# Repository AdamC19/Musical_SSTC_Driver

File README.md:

# Musical Solid-State Tesla Coil Project
These are the hardware source files for my 2022 revision of my musical solid-state Tesla coil driver. 

This is a completely analog design. No firmware!

## Concept
The concept is not far off from my previous design, except for a few notable differences.

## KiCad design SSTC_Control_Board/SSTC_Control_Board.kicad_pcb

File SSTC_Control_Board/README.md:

# Control Board

Below is a simplified block-diagram of the control board:

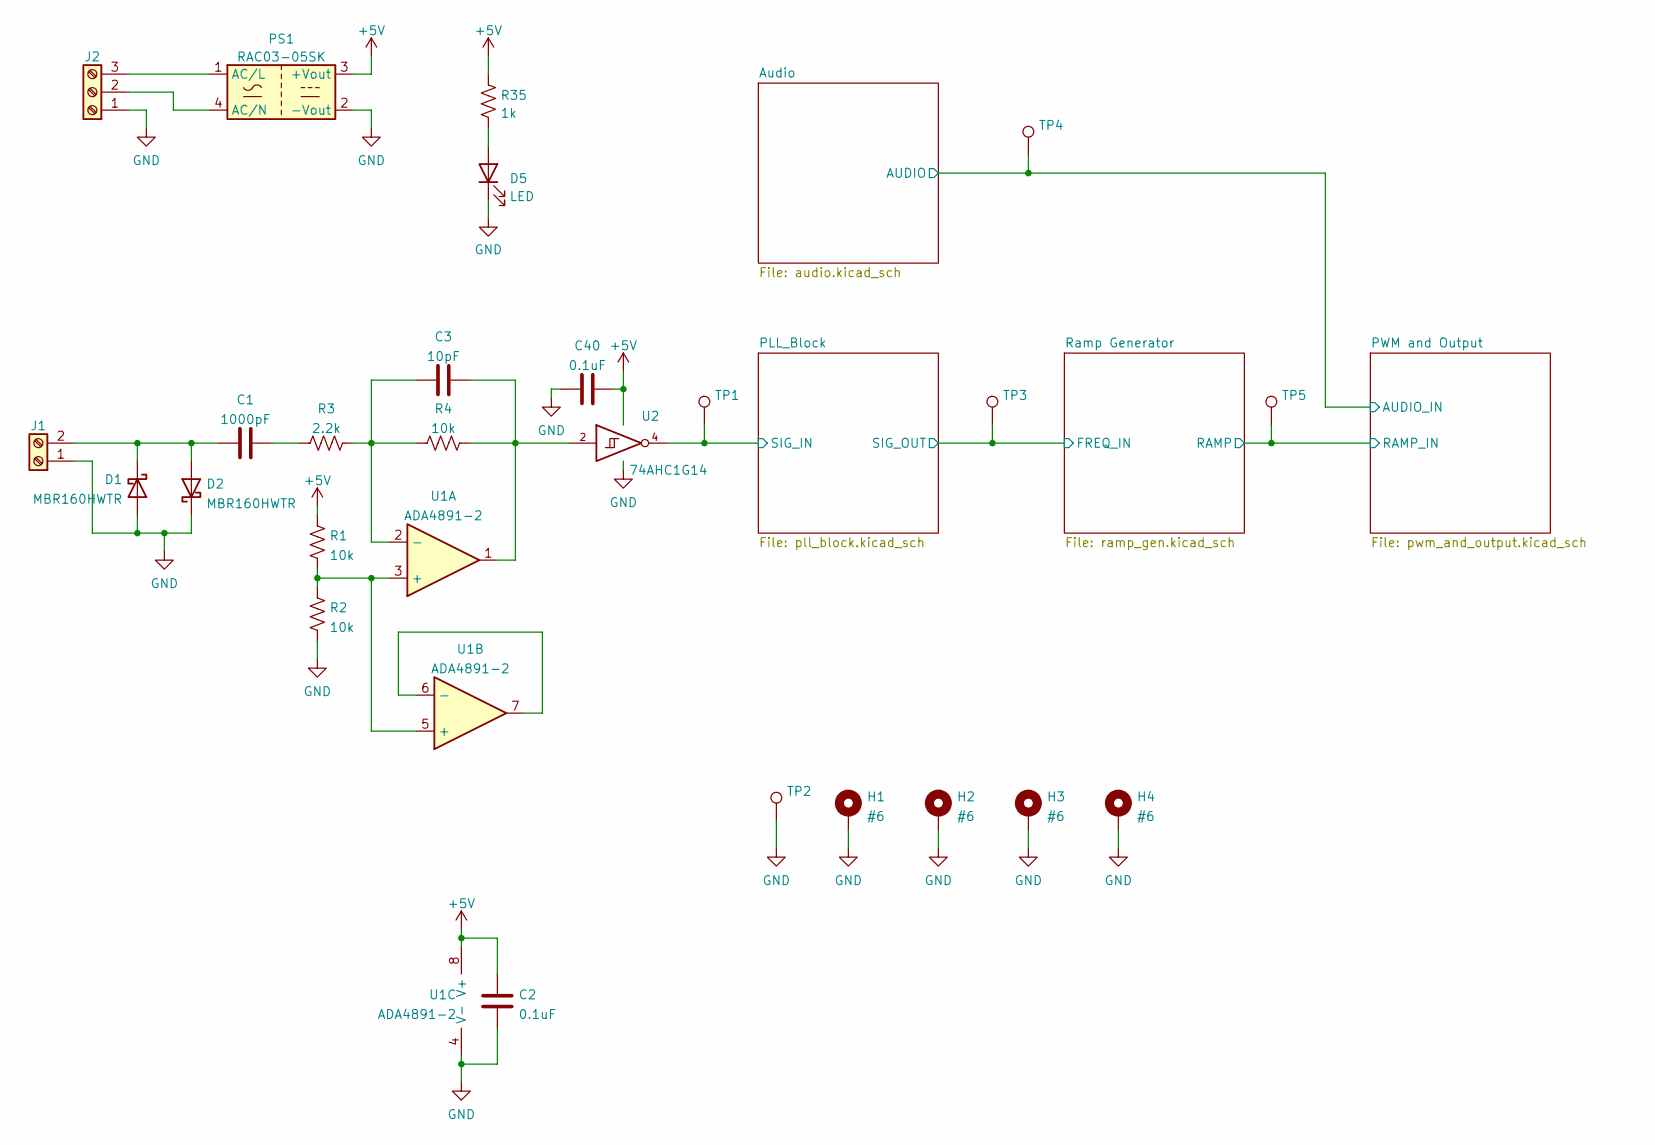
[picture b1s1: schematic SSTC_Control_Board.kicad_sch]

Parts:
C1: 1000pF; C_0603_1608Metric
C2, C40: 0.1uF; C_0603_1608Metric
C3: 10pF; C_0603_1608Metric
D1, D2: MBR160HWTR; D_SOD-123; MFG_PN MBR160HWTR
D5: LED; LED_0603_1608Metric
H1, H2, H3, H4: #6; MountingHole_3.7mm_Pad_Via
J1: Screw_Terminal_01x02; PhoenixContact_MC_1,5_2-G-3.81_1x02_P3.81mm_Horizontal
J2: Screw_Terminal_01x03; PhoenixContact_GMSTBA_2,5_3-G-7,62_1x03_P7.62mm_Horizontal
PS1: RAC03-05SK; RAC03-K; MFG_PN RAC03-05SK
R1, R2, R4: 10k; R_0805_2012Metric
R3: 2.2k; R_0805_2012Metric
R35: 1k; R_0805_2012Metric
TP1, TP2, TP3, TP4, TP5: TestPoint; TestPoint_Bridge_Pitch2.54mm_Drill1.0mm
U1: ADA4891-2; SOIC-8_3.9x4.9mm_P1.27mm
U2: 74AHC1G14; SOT-23-5

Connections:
+5V: C2.2, C40.1, PS1.3 (+Vout), R1.1, R35.2, U1.8 (V+), U2.5 (VCC); also elsewhere on the board
/Audio/AUDIO: TP4.1; also elsewhere on the board
/PLL_Block/SIG_IN: TP1.1, U2.4; also elsewhere on the board
/PLL_Block/SIG_OUT: TP3.1; also elsewhere on the board
/PWM and Output/RAMP_IN: TP5.1; also elsewhere on the board
GND: C2.1, C40.2, D1.2 (A), D2.1 (K), D5.1 (K), H1.1, H2.1, H3.1, H4.1, J1.1, J2.1, PS1.2 (-Vout), R2.2, TP2.1, U1.4 (V-), U2.3 (GND); also elsewhere on the board
unnamed: C1.1, D1.1 (K), D2.2 (A), J1.2
unnamed: C1.2, R3.1
unnamed: C3.1, R3.2, R4.1, U1.2 (-)
unnamed: C3.2, R4.2, U1.1, U2.2
unnamed: D5.2 (A), R35.1
unnamed: J2.2, PS1.4 (AC/N)
unnamed: J2.3, PS1.1 (AC/L)
unnamed: R1.2, R2.1, U1.3 (+), U1.5 (+)
unnamed: U1.6 (-), U1.7

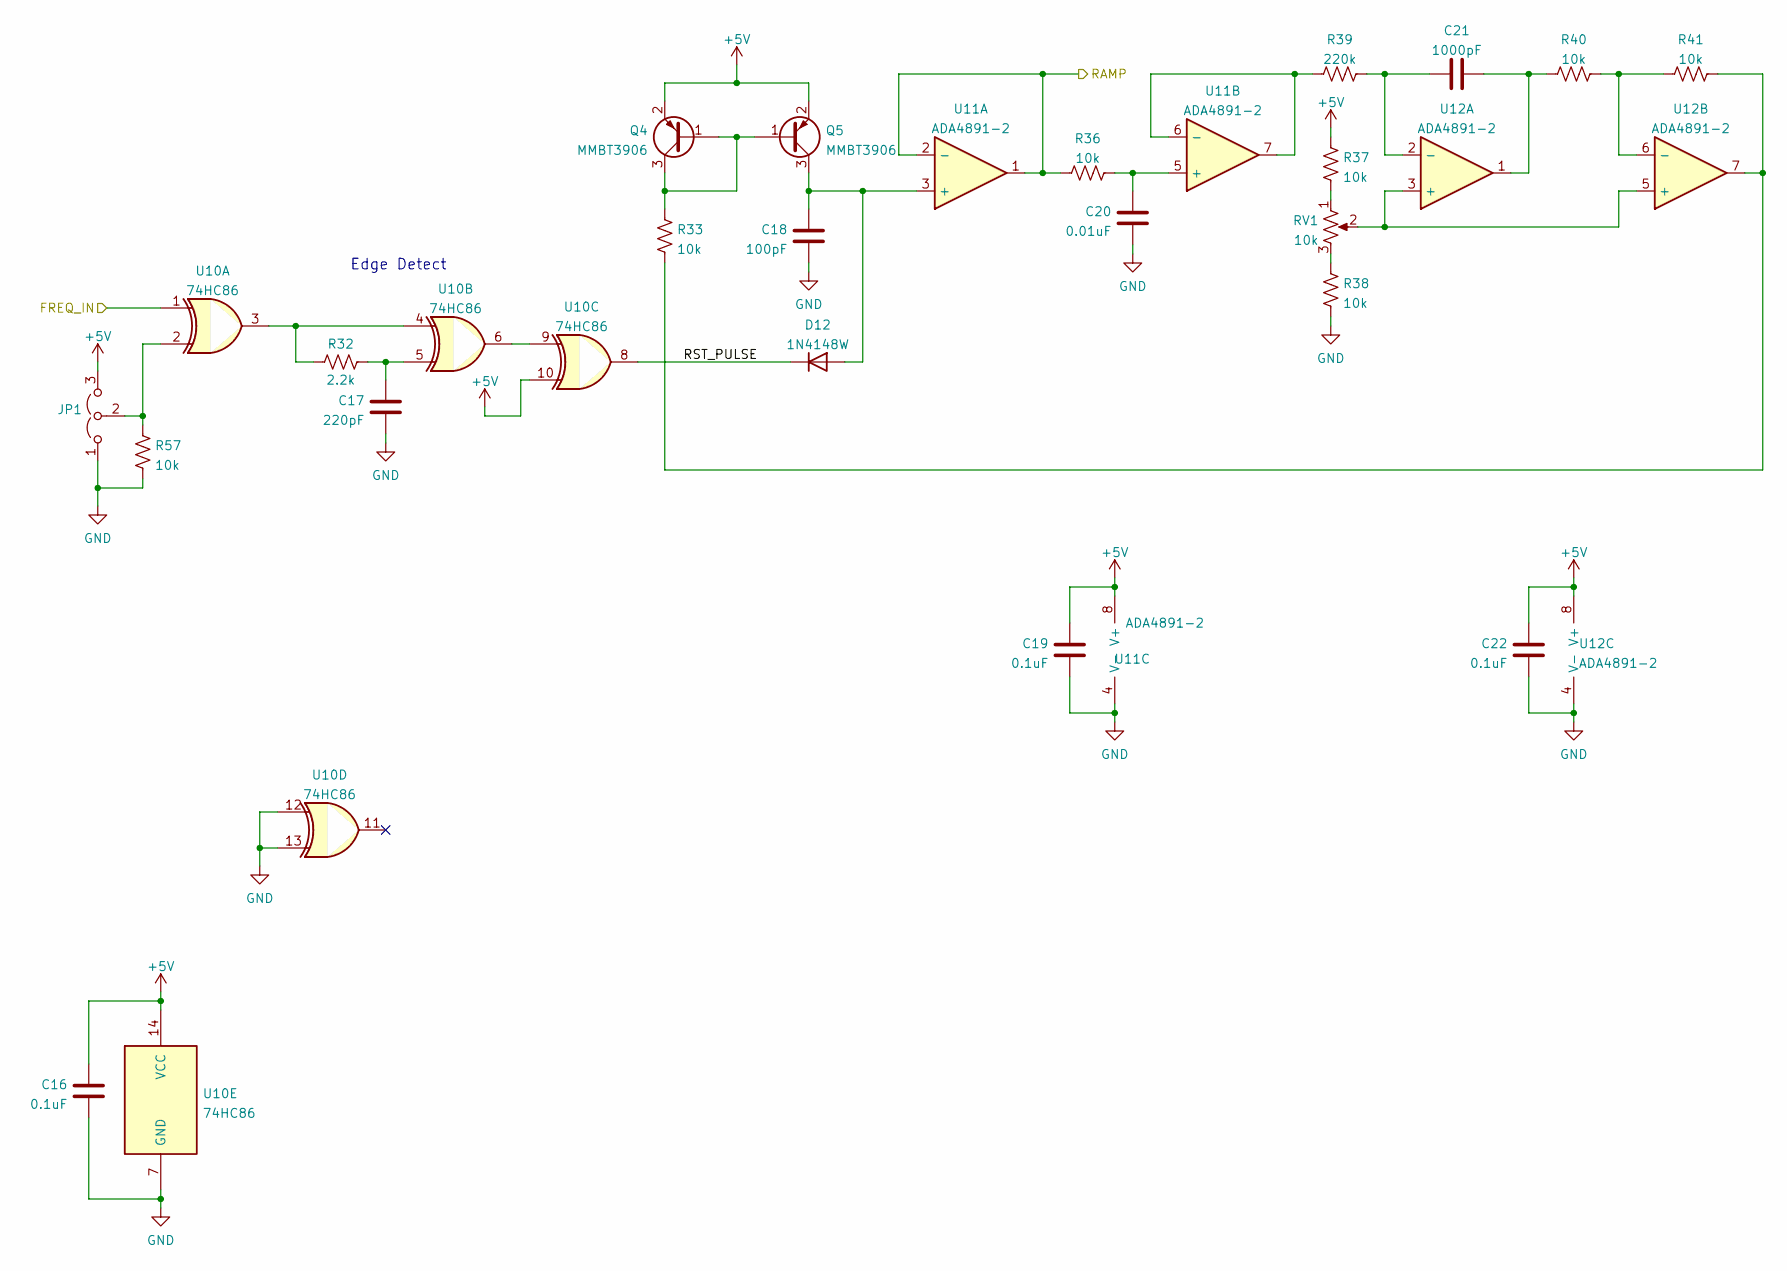
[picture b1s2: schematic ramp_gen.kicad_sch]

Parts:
C16, C19, C22: 0.1uF; C_0603_1608Metric
C17: 220pF; C_0603_1608Metric
C18: 100pF; C_0603_1608Metric
C20: 0.01uF; C_0603_1608Metric
C21: 1000pF; C_0603_1608Metric
D12: 1N4148W; D_SOD-123
JP1: Jumper_3_Open; PinHeader_1x03_P2.54mm_Vertical
Q4, Q5: MMBT3906; SOT-23
R32: 2.2k; R_0805_2012Metric
R33, R36, R37, R38, R40, R41, R57: 10k; R_0805_2012Metric
R39: 220k; R_0805_2012Metric
RV1: 10k; Potentiometer_Bourns_3386P_Vertical
U10: 74HC86; SOIC-14_3.9x8.7mm_P1.27mm
U11, U12: ADA4891-2; SOIC-8_3.9x4.9mm_P1.27mm

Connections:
+5V: C16.1, C19.1, C22.1, JP1.3 (B), Q4.2 (E), Q5.2 (E), R37.2, U10.10, U10.14 (VCC), U11.8 (V+), U12.8 (V+); also elsewhere on the board
/PLL_Block/SIG_OUT: U10.1; also elsewhere on the board
/PWM and Output/RAMP_IN: R36.1, U11.1, U11.2 (-); also elsewhere on the board
/Ramp Generator/RST_PULSE: D12.1 (K), U10.8
GND: C16.2, C17.2, C18.2, C19.2, C20.2, C22.2, JP1.1 (A), R38.1, R57.1, U10.7 (GND), U10.12, U10.13, U11.4 (V-), U12.4 (V-); also elsewhere on the board
unnamed: C17.1, R32.1, U10.5
unnamed: C18.1, D12.2 (A), Q5.3 (C), U11.3 (+)
unnamed: C20.1, R36.2, U11.5 (+)
unnamed: C21.1, R39.1, U12.2 (-)
unnamed: C21.2, R40.2, U12.1
unnamed: JP1.2 (C), R57.2, U10.2
unnamed: Q4.1 (B), Q4.3 (C), Q5.1 (B), R33.1
unnamed: R32.2, U10.3, U10.4
unnamed: R33.2, R41.1, U12.7
unnamed: R37.1, RV1.1
unnamed: R38.2, RV1.3
unnamed: R39.2, U11.6 (-), U11.7
unnamed: R40.1, R41.2, U12.6 (-)
unnamed: RV1.2, U12.3 (+), U12.5 (+)
unnamed: U10.6, U10.9

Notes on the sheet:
Edge Detect

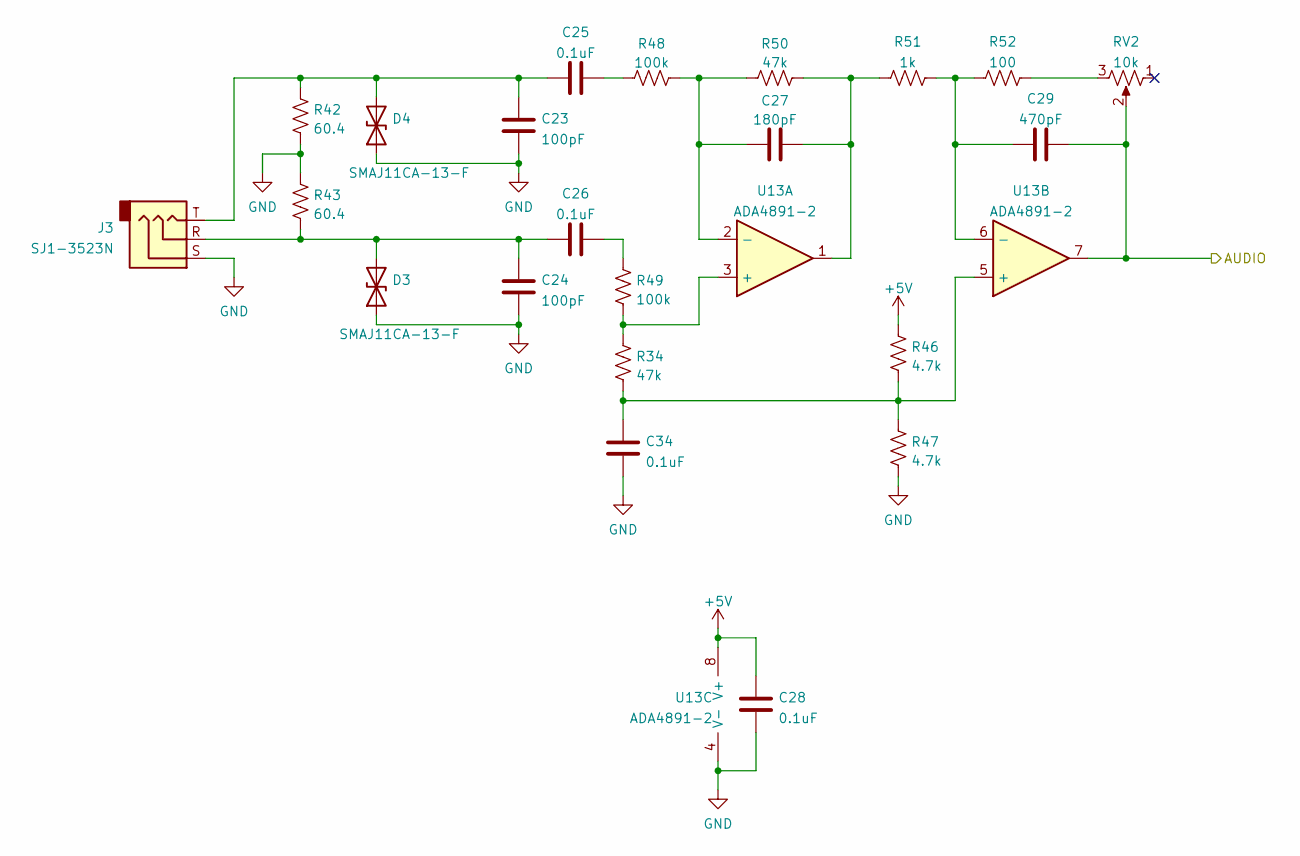
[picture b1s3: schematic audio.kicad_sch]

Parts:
C23, C24: 100pF; C_0603_1608Metric
C25, C26, C28, C34: 0.1uF; C_0603_1608Metric
C27: 180pF; C_0603_1608Metric
C29: 470pF; C_0603_1608Metric
D3, D4: SMAJ11CA-13-F; D_SMA; MFG_PN SMAJ11CA-13-F
J3: SJ1-3523N; Jack_3.5mm_CUI_SJ1-3523N_Horizontal; MFG_PN SJ1-3523N
R34, R50: 47k; R_0805_2012Metric
R42, R43: 60.4; R_0805_2012Metric
R46, R47: 4.7k; R_0805_2012Metric
R48, R49: 100k; R_0805_2012Metric
R51: 1k; R_0805_2012Metric
R52: 100; R_0805_2012Metric
RV2: 10k; Potentiometer_Bourns_PTV09A-2_Single_Horizontal; MFG_PN PTV09A-2020F-A103
U13: ADA4891-2; SOIC-8_3.9x4.9mm_P1.27mm

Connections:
+5V: C28.2, R46.2, U13.8 (V+); also elsewhere on the board
/Audio/AUDIO: C29.1, RV2.2, U13.7; also elsewhere on the board
GND: C23.1, C24.1, C28.1, C34.1, D3.1 (A1), D4.1 (A1), J3.S, R42.2, R43.1, R47.1, U13.4 (V-); also elsewhere on the board
unnamed: C23.2, C25.2, D4.2 (A2), J3.T, R42.1
unnamed: C24.2, C26.2, D3.2 (A2), J3.R, R43.2
unnamed: C25.1, R48.1
unnamed: C26.1, R49.2
unnamed: C27.1, R50.2, R51.1, U13.1
unnamed: C27.2, R48.2, R50.1, U13.2 (-)
unnamed: C29.2, R51.2, R52.2, U13.6 (-)
unnamed: C34.2, R34.1, R46.1, R47.2, U13.5 (+)
unnamed: R34.2, R49.1, U13.3 (+)
unnamed: R52.1, RV2.3

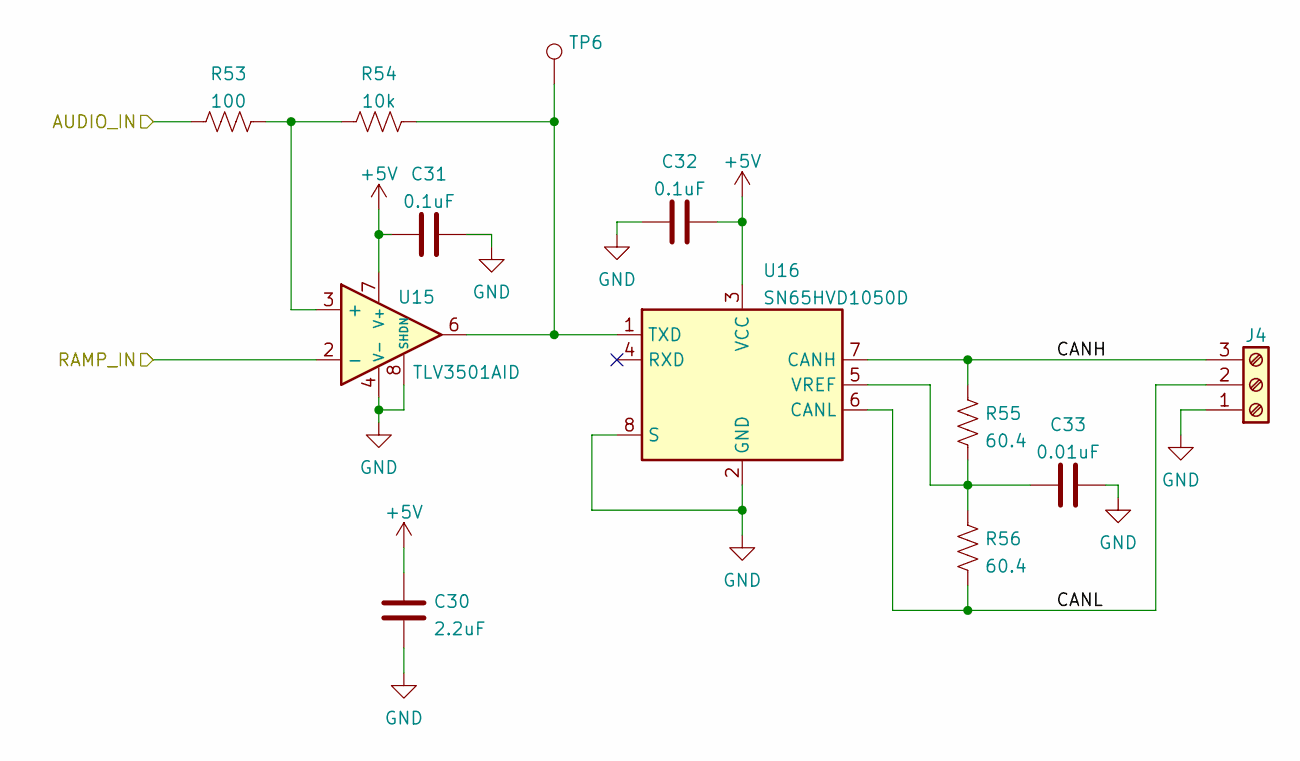
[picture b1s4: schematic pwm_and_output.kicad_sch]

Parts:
C30: 2.2uF; C_0805_2012Metric
C31, C32: 0.1uF; C_0603_1608Metric
C33: 0.01uF; C_0603_1608Metric
J4: Screw_Terminal_01x03; PhoenixContact_MC_1,5_3-G-3.81_1x03_P3.81mm_Horizontal
R53: 100; R_0805_2012Metric
R54: 10k; R_0805_2012Metric
R55, R56: 60.4; R_0805_2012Metric
TP6: TestPoint; TestPoint_Bridge_Pitch2.54mm_Drill1.0mm
U15: TLV3501AID; SOIC-8_3.9x4.9mm_P1.27mm
U16: SN65HVD1050D; SOIC-8_3.9x4.9mm_P1.27mm

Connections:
+5V: C30.2, C31.1, C32.1, U15.7 (V+), U16.3 (VCC); also elsewhere on the board
/Audio/AUDIO: R53.2; also elsewhere on the board
/PWM and Output/CANH: J4.3, R55.1, U16.7 (CANH)
/PWM and Output/CANL: J4.2, R56.2, U16.6 (CANL)
/PWM and Output/RAMP_IN: U15.2 (-); also elsewhere on the board
GND: C30.1, C31.2, C32.2, C33.2, J4.1, U15.4 (V-), U15.8 (SHDN), U16.2 (GND), U16.8 (S); also elsewhere on the board
unnamed: C33.1, R55.2, R56.1, U16.5 (VREF)
unnamed: R53.1, R54.1, U15.3 (+)
unnamed: R54.2, TP6.1, U15.6, U16.1 (TXD)

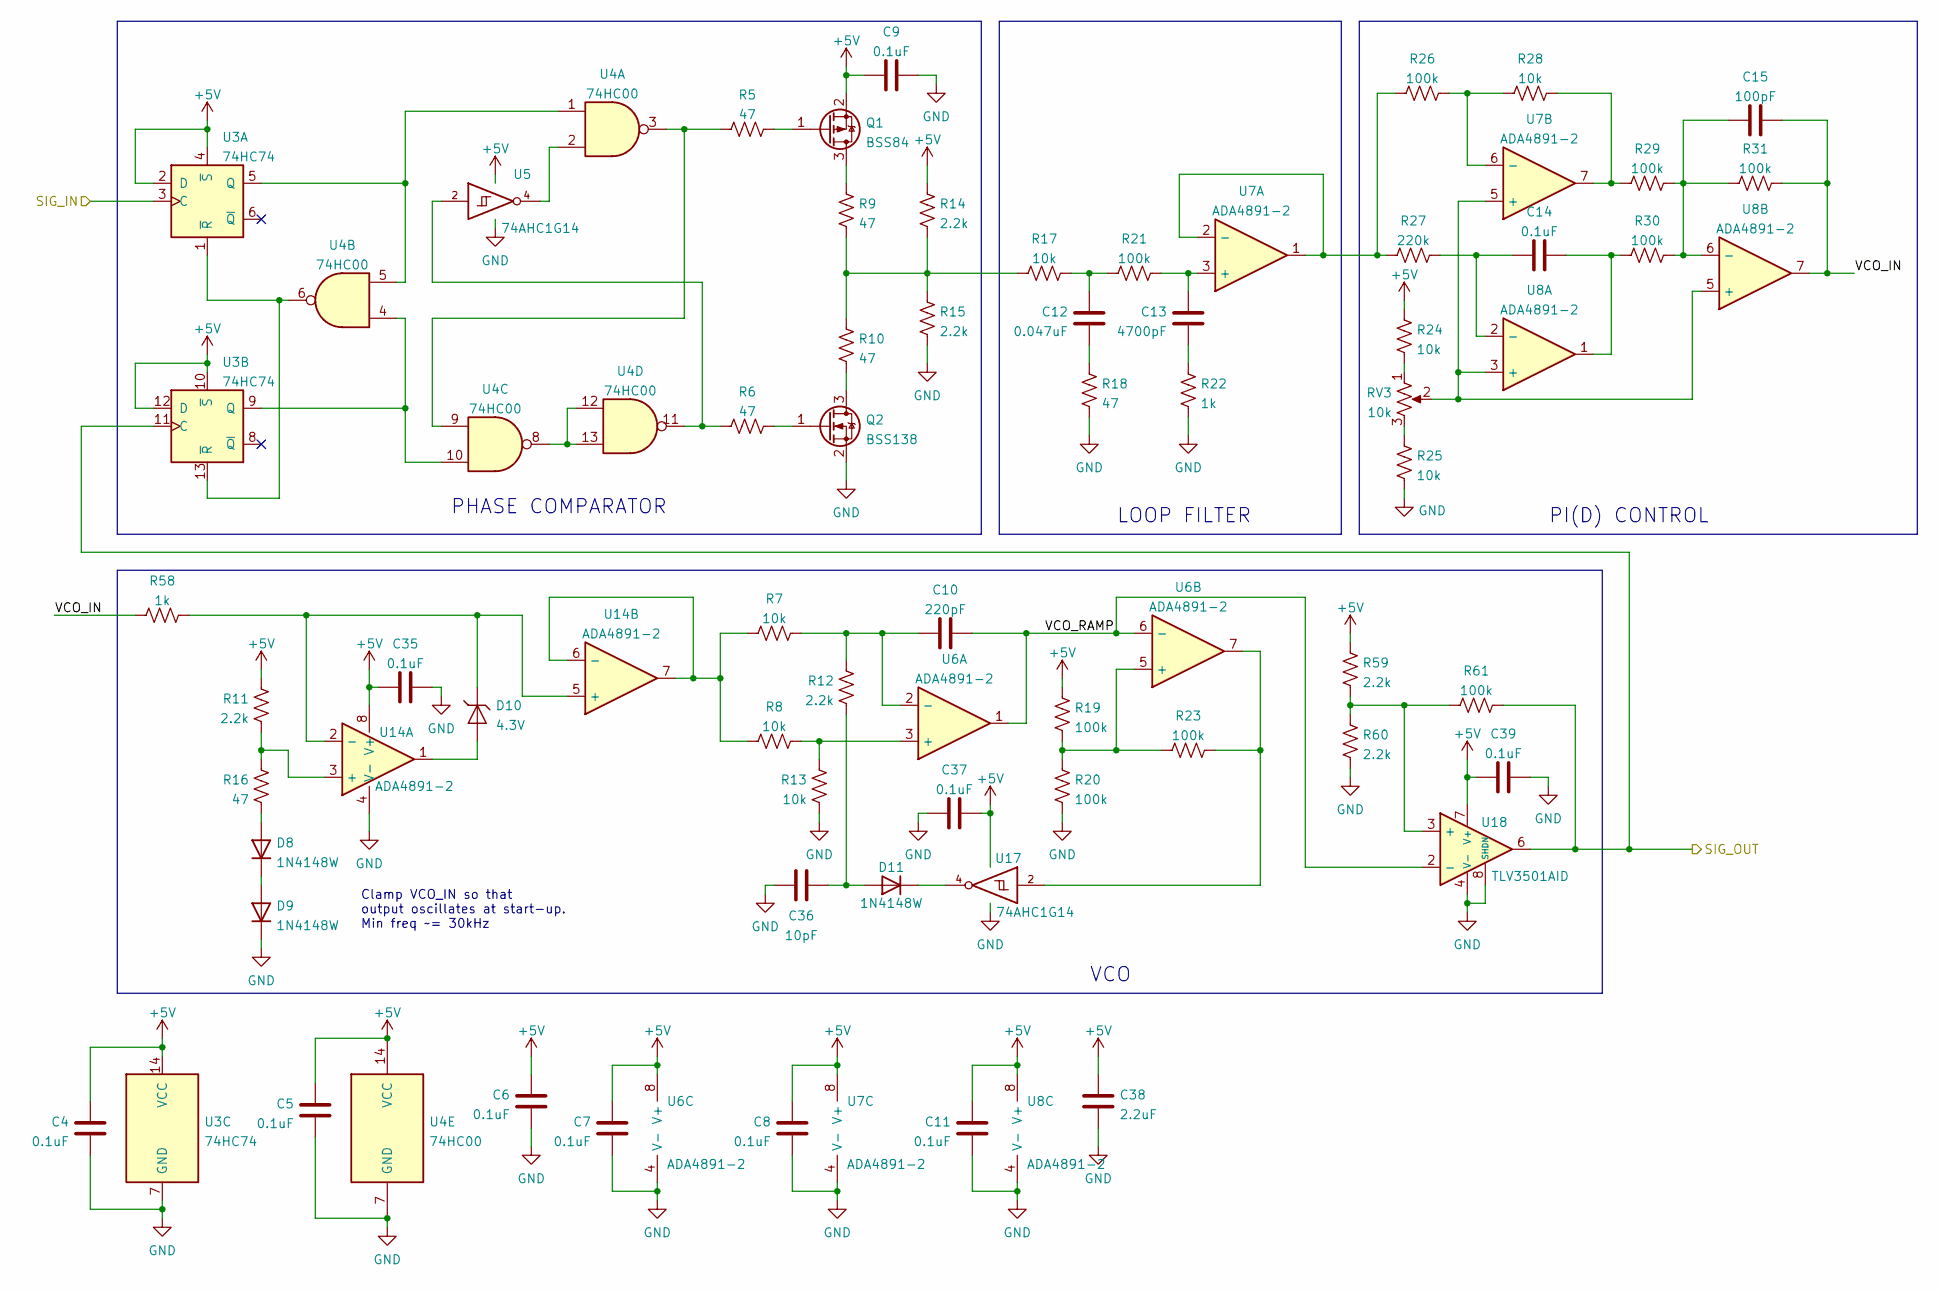
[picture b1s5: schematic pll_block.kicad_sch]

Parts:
C4, C5, C6, C7, C8, C9, C11, C14, C35, C37, C39: 0.1uF; C_0603_1608Metric
C10: 220pF; C_0603_1608Metric
C12: 0.047uF; C_0603_1608Metric
C13: 4700pF; C_0603_1608Metric
C15: 100pF; C_0603_1608Metric
C36: 10pF; C_0603_1608Metric
C38: 2.2uF; C_0805_2012Metric
D8, D9, D11: 1N4148W; D_SOD-123
D10: 4.3V; D_SOD-123; MFG_PN BZT52C4V3
Q1: BSS84; SOT-23
Q2: BSS138; SOT-23
R5, R6, R9, R10, R16, R18: 47; R_0805_2012Metric
R7, R8, R13, R17, R24, R25, R28: 10k; R_0805_2012Metric
R11, R12, R14, R15, R59, R60: 2.2k; R_0805_2012Metric
R19, R20, R21, R23, R26, R29, R30, R31, R61: 100k; R_0805_2012Metric
R22, R58: 1k; R_0805_2012Metric
R27: 220k; R_0805_2012Metric
RV3: 10k; Potentiometer_Bourns_3386P_Vertical
U3: 74HC74; SOIC-14_3.9x8.7mm_P1.27mm
U4: 74HC00; SOIC-14_3.9x8.7mm_P1.27mm
U5, U17: 74AHC1G14; SOT-23-5
U6, U7, U8, U14: ADA4891-2; SOIC-8_3.9x4.9mm_P1.27mm
U18: TLV3501AID; SOIC-8_3.9x4.9mm_P1.27mm

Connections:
+5V: C4.1, C5.1, C6.1, C7.1, C8.1, C9.1, C11.1, C35.1, C37.2, C38.2, C39.1, Q1.2 (S), R11.2, R14.2, R19.1, R24.1, R59.1, U3.2 (D), U3.4 (~S), U3.10 (~S), U3.12 (D), U3.14 (VCC), U4.14 (VCC), U5.5 (VCC), U6.8 (V+), U7.8 (V+), U8.8 (V+), U14.8 (V+), U17.5 (VCC), U18.7 (V+); also elsewhere on the board
/PLL_Block/SIG_IN: U3.3 (C); also elsewhere on the board
/PLL_Block/SIG_OUT: R61.2, U3.11 (C), U18.6; also elsewhere on the board
/PLL_Block/VCO_IN: C15.2, R31.1, R58.2, U8.7
/PLL_Block/VCO_RAMP: C10.2, U6.1, U6.6 (-), U18.2 (-)
GND: C4.2, C5.2, C6.2, C7.2, C8.2, C9.2, C11.2, C35.2, C36.1, C37.1, C38.1, C39.2, D9.1 (K), Q2.2 (S), R13.1, R15.1, R18.1, R20.2, R22.1, R25.2, R60.2, U3.7 (GND), U4.7 (GND), U5.3 (GND), U6.4 (V-), U7.4 (V-), U8.4 (V-), U14.4 (V-), U17.3 (GND), U18.4 (V-), U18.8 (SHDN); also elsewhere on the board
unnamed: C10.1, R7.2, R12.2, U6.2 (-)
unnamed: C12.1, R17.1, R21.2
unnamed: C12.2, R18.2
unnamed: C13.1, R21.1, U7.3 (+)
unnamed: C13.2, R22.2
unnamed: C14.1, R27.1, U8.2 (-)
unnamed: C14.2, R30.2, U8.1
unnamed: C15.1, R29.1, R30.1, R31.2, U8.6 (-)
unnamed: C36.2, D11.2 (A), R12.1
unnamed: D8.1 (K), D9.2 (A)
unnamed: D8.2 (A), R16.1
unnamed: D10.1 (K), R58.1, U14.2 (-), U14.5 (+)
unnamed: D10.2 (A), U14.1
unnamed: D11.1 (K), U17.4
unnamed: Q1.1 (G), R5.2
unnamed: Q1.3 (D), R9.2
unnamed: Q2.1 (G), R6.2
unnamed: Q2.3 (D), R10.1
unnamed: R5.1, U4.3, U4.9
unnamed: R6.1, U4.11, U5.2
unnamed: R7.1, R8.2, U14.6 (-), U14.7
unnamed: R9.1, R10.2, R14.1, R15.2, R17.2
unnamed: R11.1, R16.2, U14.3 (+)
unnamed: R8.1, R13.2, U6.3 (+)
unnamed: R19.2, R20.1, R23.1, U6.5 (+)
unnamed: R23.2, U6.7, U17.2
unnamed: R24.2, RV3.1
unnamed: R25.1, RV3.3
unnamed: R26.1, R28.2, U7.6 (-)
unnamed: R26.2, R27.2, U7.1, U7.2 (-)
unnamed: R28.1, R29.2, U7.7
unnamed: R59.2, R60.1, R61.1, U18.3 (+)
unnamed: RV3.2, U7.5 (+), U8.3 (+), U8.5 (+)
unnamed: U3.1 (~R), U3.13 (~R), U4.6
unnamed: U3.5 (Q), U4.1, U4.5
unnamed: U3.9 (Q), U4.4, U4.10
unnamed: U4.2, U5.4
unnamed: U4.8, U4.12, U4.13

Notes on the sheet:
LOOP FILTER
Clamp VCO_IN so that output oscillates at start-up. Min freq ~= 30kHz
VCO
PI(D) CONTROL
PHASE COMPARATOR

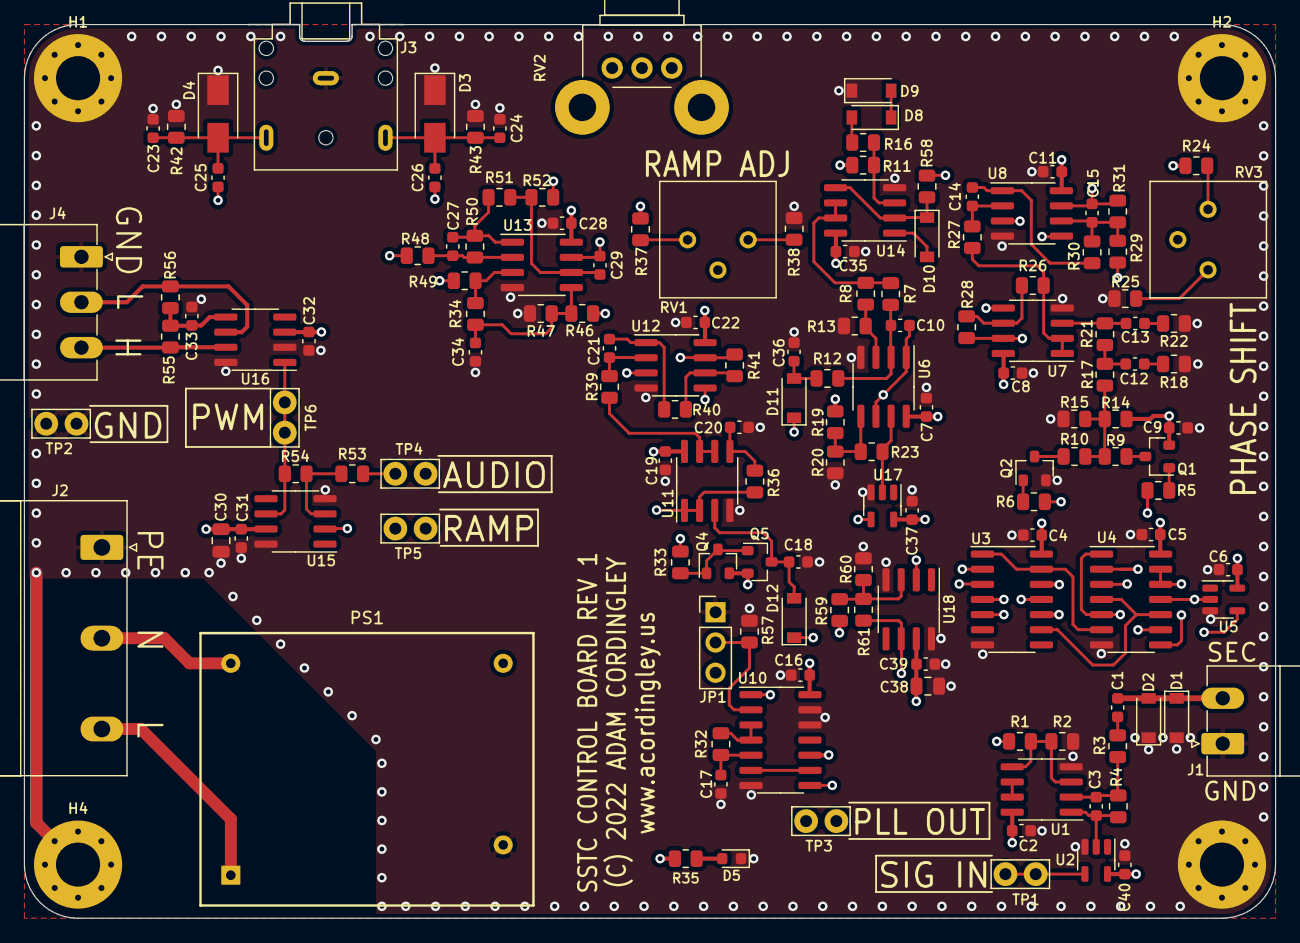
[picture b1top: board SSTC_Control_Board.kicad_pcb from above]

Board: 4 copper layers, 105.0 x 75.0 mm, 149 parts (0 on the bottom side), 86 nets.

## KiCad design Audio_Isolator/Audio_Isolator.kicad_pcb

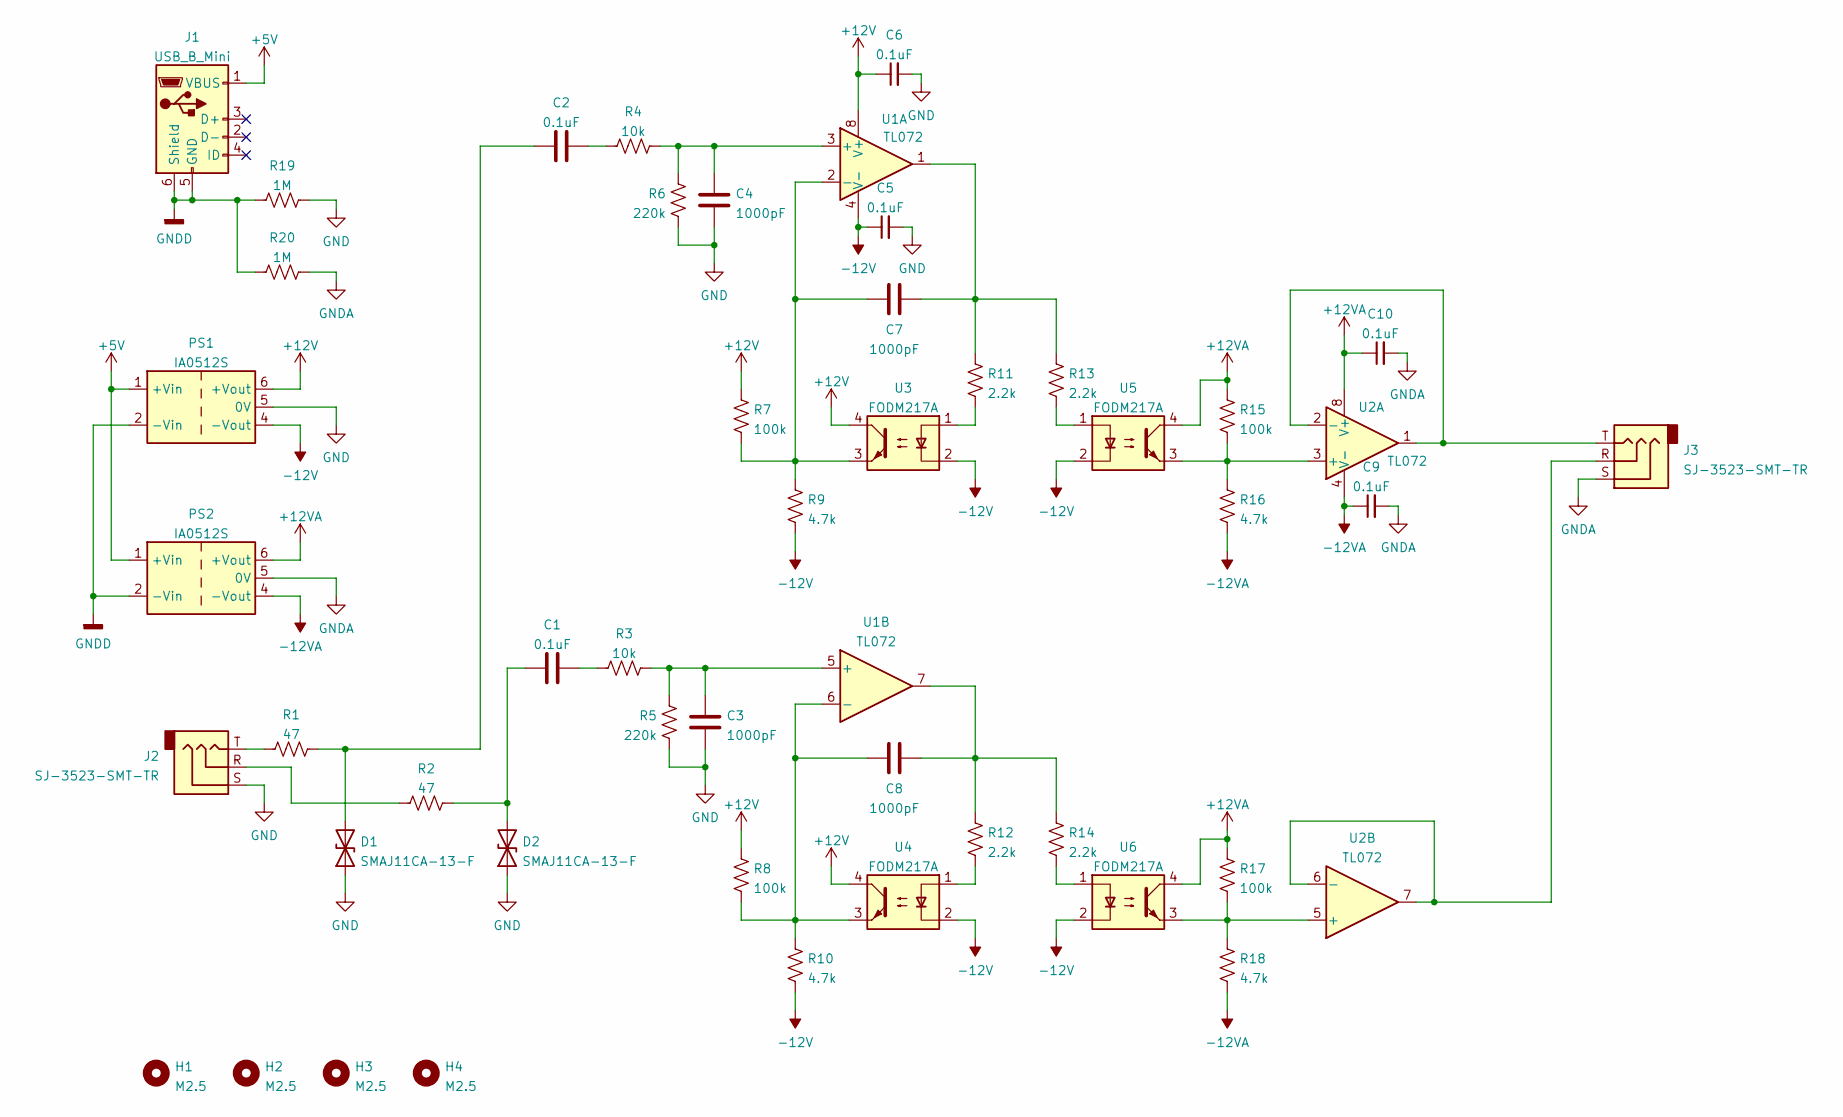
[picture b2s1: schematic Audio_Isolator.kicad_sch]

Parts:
C1, C2, C5, C6, C9, C10: 0.1uF; C_0603_1608Metric
C3, C4, C7, C8: 1000pF; C_0603_1608Metric
D1, D2: SMAJ11CA-13-F; D_SMA; MFG_PN SMAJ11CA-13-F
H1, H2, H3, H4: M2.5; MountingHole_2.7mm_M2.5_Pad
J1: USB_B_Mini; USB_Mini-B_Wuerth_65100516121_Horizontal
J2, J3: SJ-3523-SMT-TR; Jack_3.5mm_CUI_SJ-3523-SMT_Horizontal; MFG_PN SJ-3523-SMT-TR
PS1, PS2: IA0512S; Converter_DCDC_XP_POWER-IAxxxxS_THT
R1, R2: 47; R_0805_2012Metric
R3, R4: 10k; R_0805_2012Metric
R5, R6: 220k; R_0805_2012Metric
R7, R8, R15, R17: 100k; R_0805_2012Metric
R9, R10, R16, R18: 4.7k; R_0805_2012Metric
R11, R12, R13, R14: 2.2k; R_0805_2012Metric
R19, R20: 1M; R_2512_6332Metric
U1, U2: TL072; SOIC-8_3.9x4.9mm_P1.27mm
U3, U4, U5, U6: FODM217A; SOP-4_4.4x2.6mm_P1.27mm

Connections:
+5V: J1.1 (VBUS), PS1.1 (+Vin), PS2.1 (+Vin)
+12V: C6.1, PS1.6 (+Vout), R7.1, R8.1, U1.8 (V+), U3.4, U4.4
+12VA: C10.1, PS2.6 (+Vout), R15.1, R17.1, U2.8 (V+), U5.4, U6.4
-12V: C5.1, PS1.4 (-Vout), R9.2, R10.2, U1.4 (V-), U3.2, U4.2, U5.2, U6.2
-12VA: C9.1, PS2.4 (-Vout), R16.2, R18.2, U2.4 (V-)
GND: C3.2, C4.2, C5.2, C6.2, D1.1 (A1), D2.1 (A1), J2.S, PS1.5 (0V), R5.2, R6.2, R19.2
GNDA: C9.2, C10.2, J3.S, PS2.5 (0V), R20.2
GNDD: J1.5 (GND), J1.6 (Shield), PS1.2 (-Vin), PS2.2 (-Vin), R19.1, R20.1
unnamed: C1.1, D2.2 (A2), R2.2
unnamed: C1.2, R3.1
unnamed: C2.1, D1.2 (A2), R1.2
unnamed: C2.2, R4.1
unnamed: J2.R, R2.1
unnamed: J2.T, R1.1
unnamed: R11.2, U3.1
unnamed: R12.2, U4.1
unnamed: R13.2, U5.1
unnamed: R14.2, U6.1
unnamed: C7.1, R11.1, R13.1, U1.1
unnamed: C7.2, R7.2, R9.1, U1.2 (-), U3.3
unnamed: C4.1, R4.2, R6.1, U1.3 (+)
unnamed: C3.1, R3.2, R5.1, U1.5 (+)
unnamed: C8.2, R8.2, R10.1, U1.6 (-), U4.3
unnamed: C8.1, R12.1, R14.1, U1.7
unnamed: J3.T, U2.1, U2.2 (-)
unnamed: R15.2, R16.1, U2.3 (+), U5.3
unnamed: R17.2, R18.1, U2.5 (+), U6.3
unnamed: J3.R, U2.6 (-), U2.7

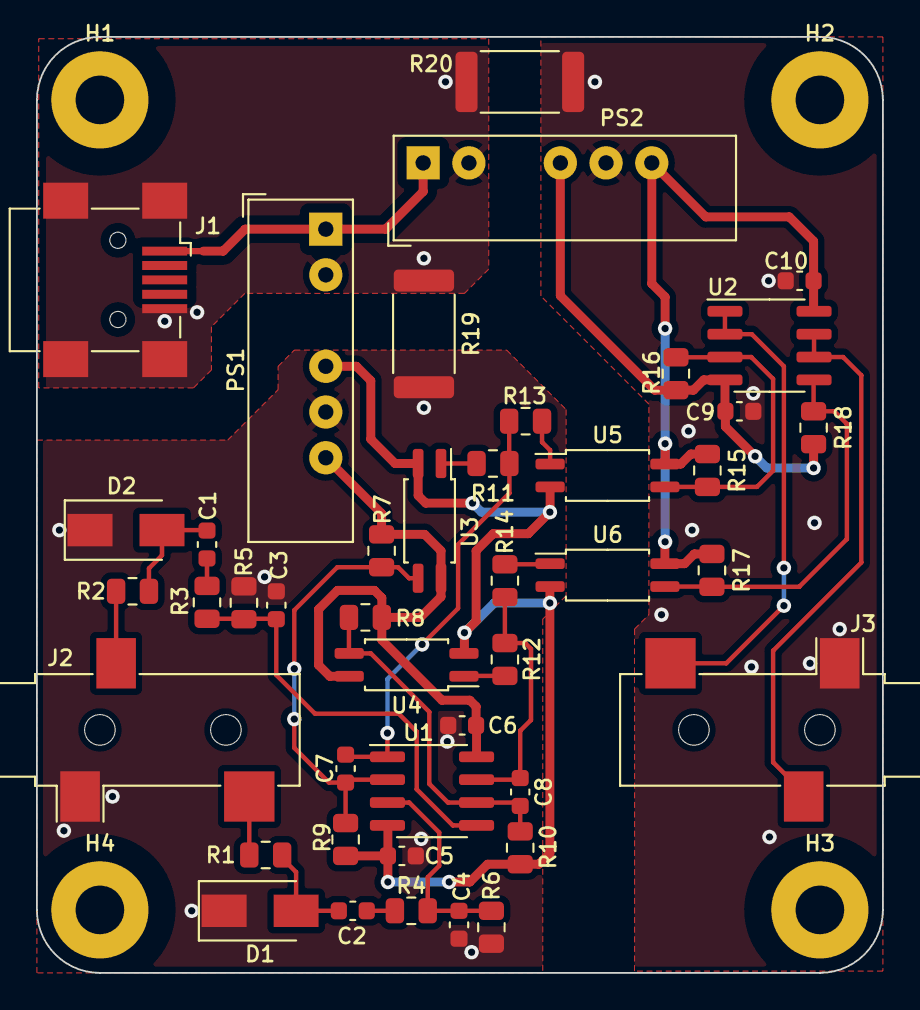
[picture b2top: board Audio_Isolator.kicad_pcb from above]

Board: 2 copper layers, 47.0 x 52.0 mm, 47 parts (0 on the bottom side), 28 nets.

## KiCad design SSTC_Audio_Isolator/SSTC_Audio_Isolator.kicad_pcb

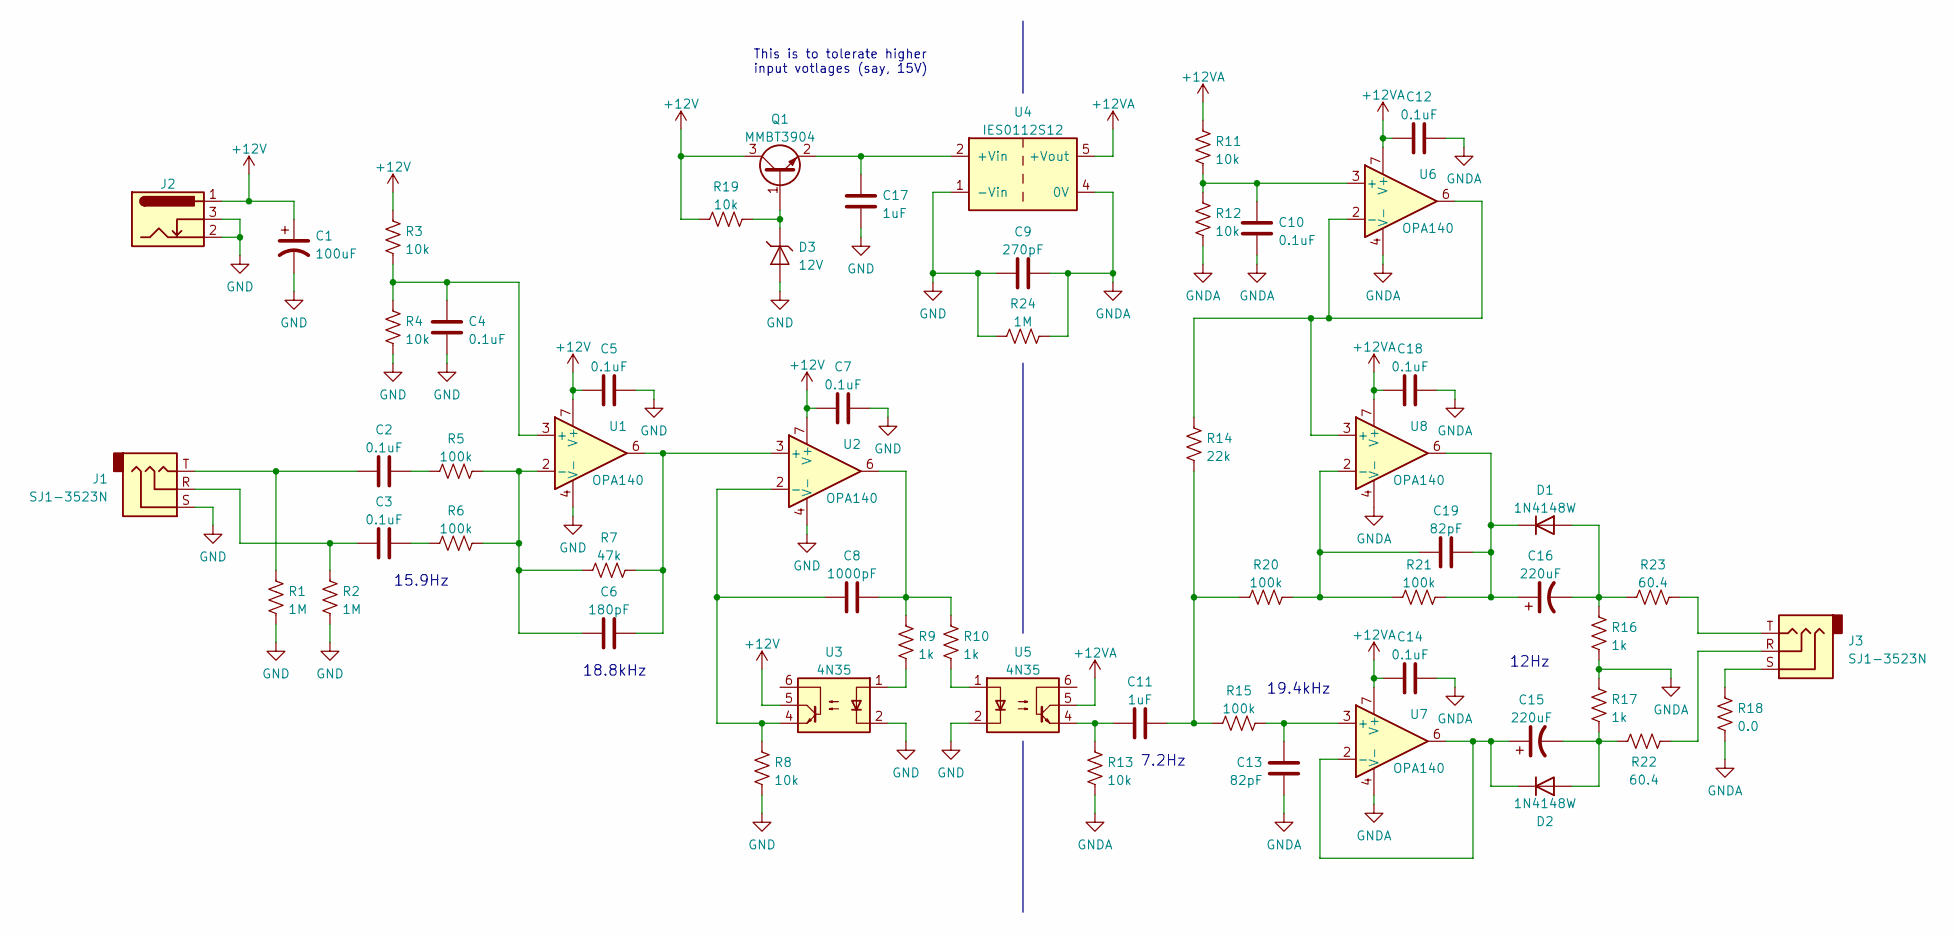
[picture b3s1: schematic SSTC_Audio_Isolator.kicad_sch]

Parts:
C1: 100uF; CP_Elec_6.3x9.9
C2, C3, C4, C5, C7, C10, C12, C14, C18: 0.1uF; C_0603_1608Metric
C6: 180pF; C_0603_1608Metric
C8: 1000pF; C_0603_1608Metric
C9: 270pF; C_1206_3216Metric
C11, C17: 1uF; C_0805_2012Metric
C13, C19: 82pF; C_0603_1608Metric
C15, C16: 220uF; CP_Elec_10x10
D1, D2: 1N4148W; D_SOD-123
D3: 12V; D_SOD-123
J1, J3: SJ1-3523N; Jack_3.5mm_CUI_SJ1-3523N_Horizontal; MFG_PN SJ1-3523N
J2: Barrel_Jack_Switch; BarrelJack_CUI_PJ-066A
Q1: MMBT3904; SOT-23
R1, R2: 1M; R_0603_1608Metric
R3, R4, R8, R11, R12, R13, R19: 10k; R_0603_1608Metric
R5, R6, R15, R20, R21: 100k; R_0603_1608Metric
R7: 47k; R_0603_1608Metric
R9, R10, R16, R17: 1k; R_0603_1608Metric
R14: 22k; R_0603_1608Metric
R18: 0.0; R_0805_2012Metric
R22, R23: 60.4; R_0805_2012Metric
R24: 1M; R_1206_3216Metric
U1, U2, U6, U7, U8: OPA140; SOIC-8_3.9x4.9mm_P1.27mm
U3, U5: 4N35; DIP-6_W7.62mm
U4: IES0112S12; XP_Power_ISE

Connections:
+12V: C1.1, C5.1, C7.1, J2.1, Q1.3 (C), R3.1, R19.1, U1.7 (V+), U2.7 (V+), U3.5
+12VA: C12.1, C14.1, C18.1, R11.2, U4.5 (+Vout), U5.5, U6.7 (V+), U7.7 (V+), U8.7 (V+)
GND: C1.2, C4.1, C5.2, C7.2, C9.1, C17.1, D3.2 (A), J1.S, J2.2, J2.3, R1.1, R2.1, R4.2, R8.1, R24.2, U1.4 (V-), U2.4 (V-), U3.2, U4.1 (-Vin), U5.2
GNDA: C9.2, C10.1, C12.2, C13.1, C14.2, C18.2, R12.1, R13.1, R16.1, R17.2, R18.1, R24.1, U4.4 (0V), U6.4 (V-), U7.4 (V-), U8.4 (V-)
unnamed: C2.1, J1.T, R1.2
unnamed: C2.2, R5.1
unnamed: C3.1, J1.R, R2.2
unnamed: C3.2, R6.1
unnamed: C4.2, R3.2, R4.1, U1.3 (+)
unnamed: C6.1, R5.2, R6.2, R7.1, U1.2 (-)
unnamed: C6.2, R7.2, U1.6, U2.3 (+)
unnamed: C8.1, R8.2, U2.2 (-), U3.4
unnamed: C8.2, R9.1, R10.1, U2.6
unnamed: C10.2, R11.1, R12.2, U6.3 (+)
unnamed: C11.1, R13.2, U5.4
unnamed: C11.2, R14.1, R15.2, R20.2
unnamed: C13.2, R15.1, U7.3 (+)
unnamed: C15.1, D2.1 (K), U7.2 (-), U7.6
unnamed: C15.2, D2.2 (A), R17.1, R22.2
unnamed: C16.1, C19.1, D1.1 (K), R21.1, U8.6
unnamed: C16.2, D1.2 (A), R16.2, R23.2
unnamed: C17.2, Q1.2 (E), U4.2 (+Vin)
unnamed: C19.2, R20.1, R21.2, U8.2 (-)
unnamed: D3.1 (K), Q1.1 (B), R19.2
unnamed: J3.R, R22.1
unnamed: J3.S, R18.2
unnamed: J3.T, R23.1
unnamed: R9.2, U3.1
unnamed: R10.2, U5.1
unnamed: R14.2, U6.2 (-), U6.6, U8.3 (+)

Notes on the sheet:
19.4kHz
7.2Hz
15.9Hz
This is to tolerate higher input votlages (say, 15V)
12Hz
18.8kHz

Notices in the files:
SSTC_Audio_Isolator/SSTC_Audio_Isolator.kicad_pcb:
AUDIO ISOLATOR | (C) 2022 ADAM CORDINGLEY | www.acordingley.us
SSTC_Full_Bridge_Driver/SSTC_Full_Bridge_Driver.kicad_pcb:
(C) 2022 ADAM CORDINGELY
